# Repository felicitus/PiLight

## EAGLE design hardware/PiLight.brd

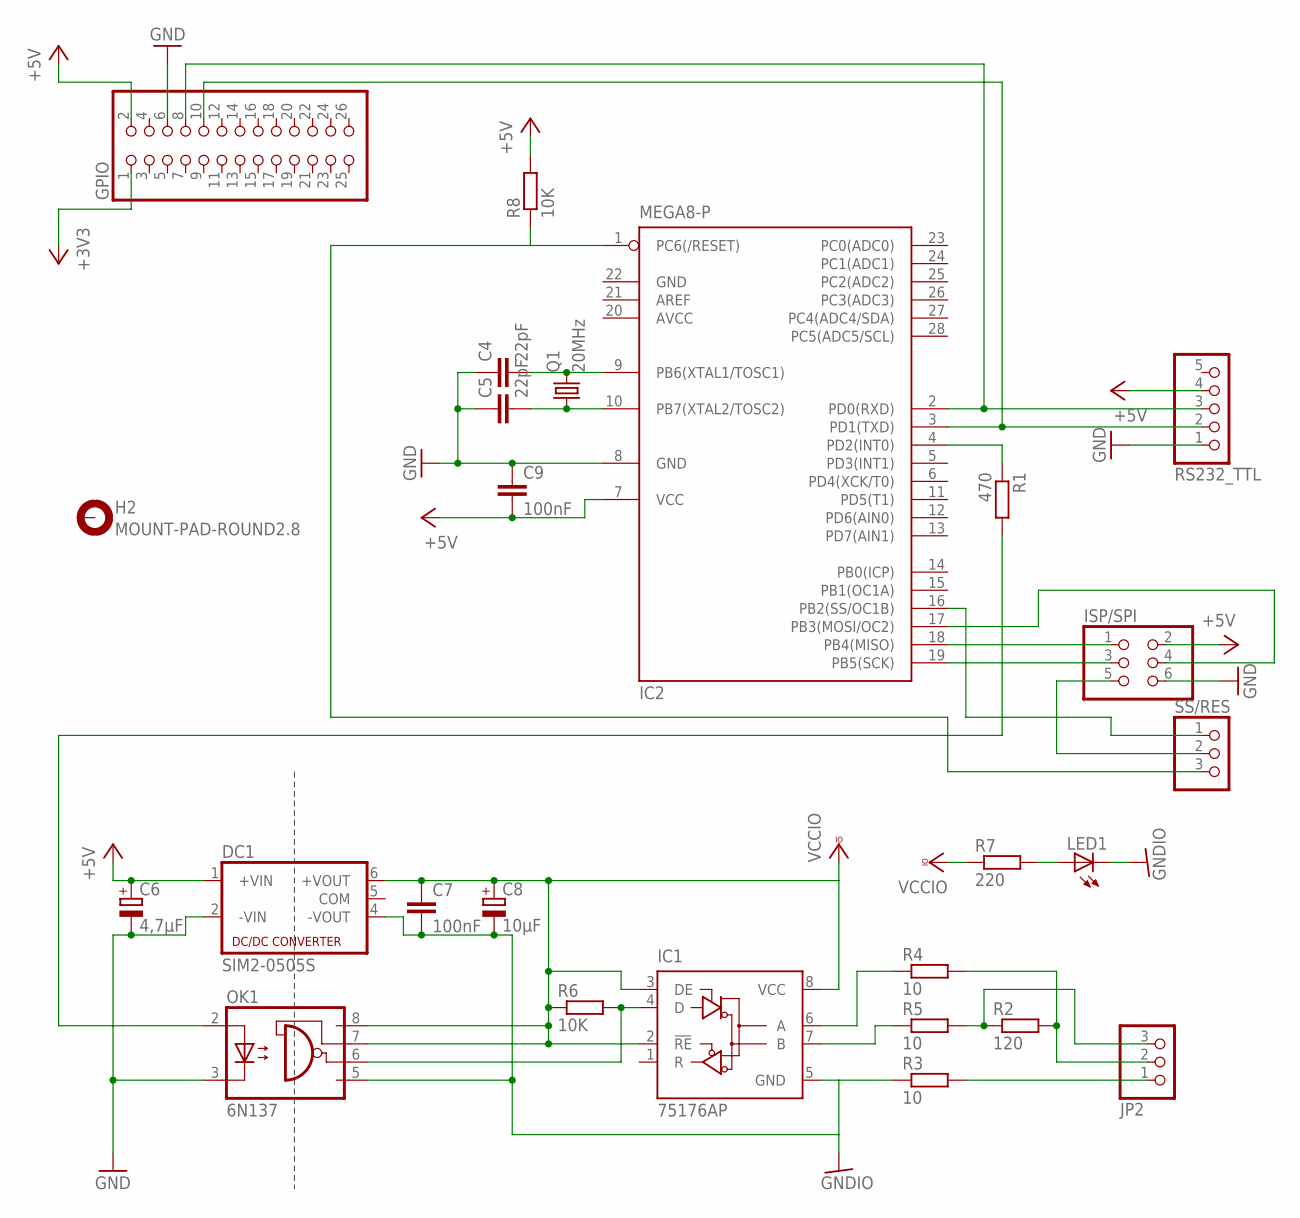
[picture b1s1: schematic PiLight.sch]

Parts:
C4, C5: 22pF; C025-025X050
C6: 4,7µF; E2,5-5
C7, C9: 100nF; C025-025X050
C8: 10µF; E2,5-5
DC1: SIM2-0505S; NMA
GPIO: PINHD-2X13; 2X13
H2: MOUNT-PAD-ROUND2.8; 2,8-PAD
IC1: 75176AP; DIL08
IC2: MEGA8-P; DIL28-3
ISP/SPI: PINHD-2X3; 2X03
JP2: PINHD-1X3; 1X03
LED1: LED3MM
OK1: 6N137; DIL08
Q1: 20MHz; HC49/S
R1: 470; 0207/10
R2: 120; 0207/10
R3, R4, R5: 10; 0207/10
R6, R8: 10K; 0207/10
R7: 220; 0207/10
RS232_TTL: PINHD-1X5; 1X05
SS/RES: PINHD-1X3; 1X03

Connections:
+3V3: GPIO.1
+5V: C6.+, C9.2, DC1.1 (+VIN), GPIO.2, IC2.7 (VCC), ISP/SPI.2, R8.2, RS232_TTL.4
AVCC: IC2.20 (AVCC)
GND: C4.1, C5.1, C6.-, C9.1, DC1.2 (-VIN), GPIO.6, IC2.8 (GND), IC2.22 (GND), ISP/SPI.6, OK1.3 (C), RS232_TTL.1
GNDIO: C7.2, C8.-, DC1.4 (-VOUT), IC1.5 (GND), LED1.K (C), OK1.5 (GND), R3.1
unnamed: IC2.1 (PC6(/RESET)), R8.1, SS/RES.3
unnamed: IC2.17 (PB3(MOSI/OC2)), ISP/SPI.4
unnamed: IC2.18 (PB4(MISO)), ISP/SPI.1
unnamed: IC2.19 (PB5(SCK)), ISP/SPI.3
unnamed: C4.2, IC2.9 (PB6(XTAL1/TOSC1)), Q1.2
unnamed: GPIO.8, IC2.2 (PD0(RXD)), RS232_TTL.3
unnamed: GPIO.10, IC2.3 (PD1(TXD)), RS232_TTL.2
unnamed: ISP/SPI.5, SS/RES.2
unnamed: C5.2, IC2.10 (PB7(XTAL2/TOSC2)), Q1.1
unnamed: IC2.16 (PB2(SS/OC1B)), SS/RES.1
unnamed: OK1.2 (A), R1.2
unnamed: LED1.A, R7.2
unnamed: IC2.4 (PD2(INT0)), R1.1
unnamed: IC1.6 (A), R4.1
unnamed: IC1.7 (B), R5.1
unnamed: JP2.1, R3.2
unnamed: JP2.2, R2.2, R4.2
unnamed: JP2.3, R2.1, R5.2
unnamed: IC1.4 (D), OK1.6 (VO), R6.2
VCCIO: C7.1, C8.+, DC1.6 (+VOUT), IC1.2 (!RE), IC1.3 (DE), IC1.8 (VCC), OK1.7 (VE), OK1.8 (VCC), R6.1, R7.1

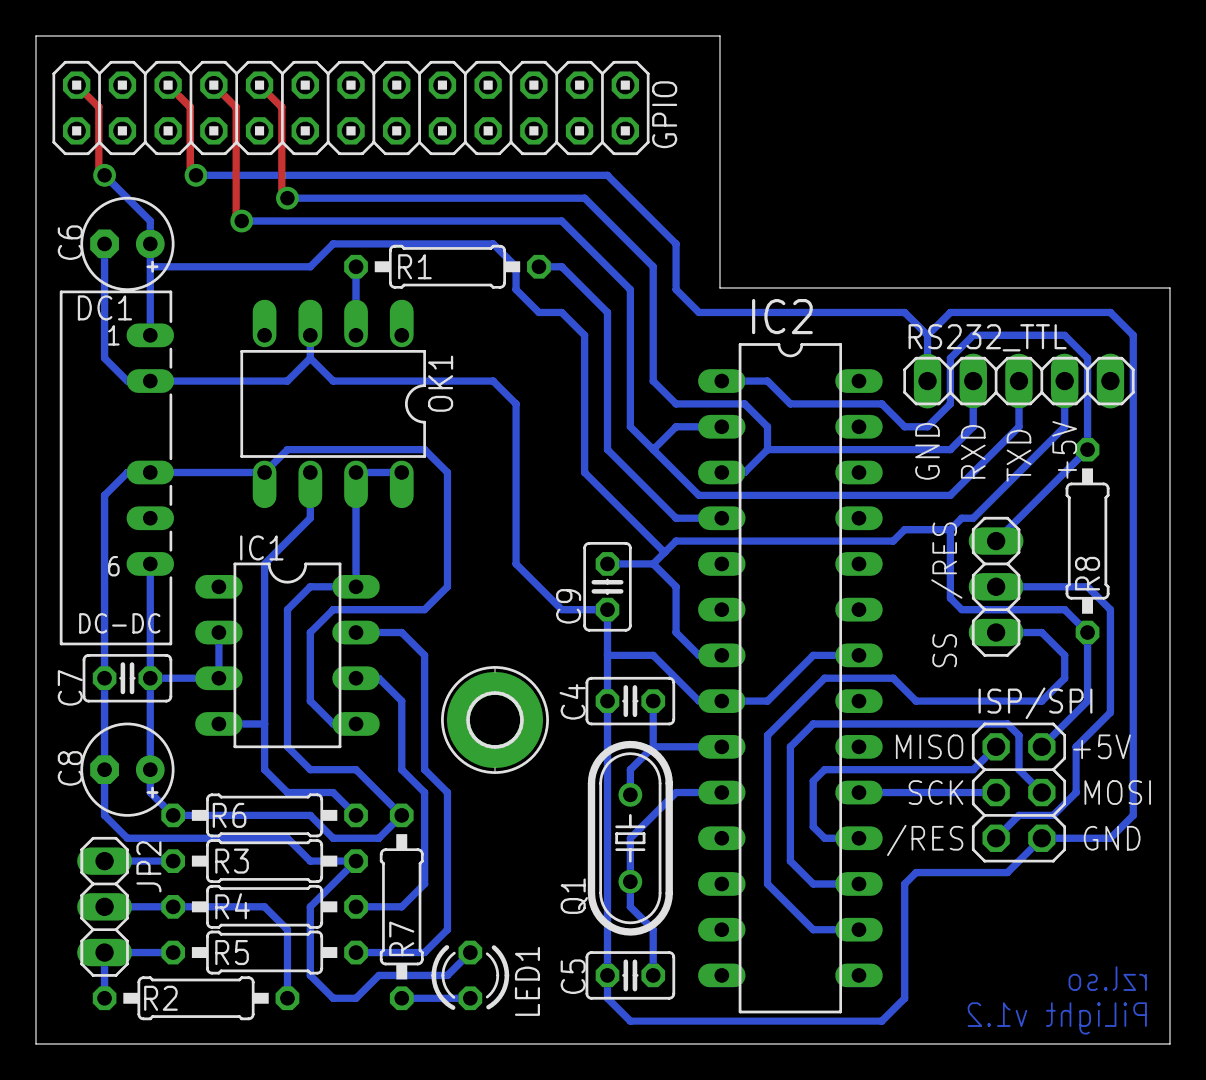
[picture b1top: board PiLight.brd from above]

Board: 2 copper layers, 63.0 x 56.0 mm, 26 parts (0 on the bottom side), 23 nets.

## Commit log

2013-05-14 Added firmware files
2013-05-14 Added schematics and board files
2013-08-20 Removed version information from filename
2013-08-20 Moved R8 so that it does not interfere with ISP/IPS head. Also moved label for LED1
